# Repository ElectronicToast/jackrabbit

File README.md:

# jackrabbit

RP2040 16-channel 100 MHz logic analyzer

## Description
Jackrabbit is a RP2040-based 16-channel logic analyzer in a tiny 1.8" by 1.2" form factor. All digital inputs are buffered for compatibility with both 3V3 and 5V logic. Boot mode select and reset buttons are provided for convenience, and the ADC inputs and SWD pins are broken out. A USB-C connector is present for firmware updates and serial data.

## Documentation
- [Schematic](https://github.com/ElectronicToast/jackrabbit/blob/main/doc/jackrabbit.pdf)
- Fab print [front](https://github.com/ElectronicToast/jackrabbit/blob/main/doc/jackrabbit-f.pdf) and [back](https://github.com/ElectronicToast/jackrabbit/blob/main/doc/jackrabbit-b.pdf)
- [Interactive BOM](http://htmlpreview.github.io/?https://github.com/ElectronicToast/jackrabbit/blob/main/doc/ibom.html)

## Contributors
- Brian Cruz - BS EE, Caltech, 2023
- Brandon Gong - BS CECS, USC, 2024
- Ray Sun - BS EE, Caltech, 2020; PhD EE, USC, 2026

## Licensing
This project is released under the terms of the MIT License.

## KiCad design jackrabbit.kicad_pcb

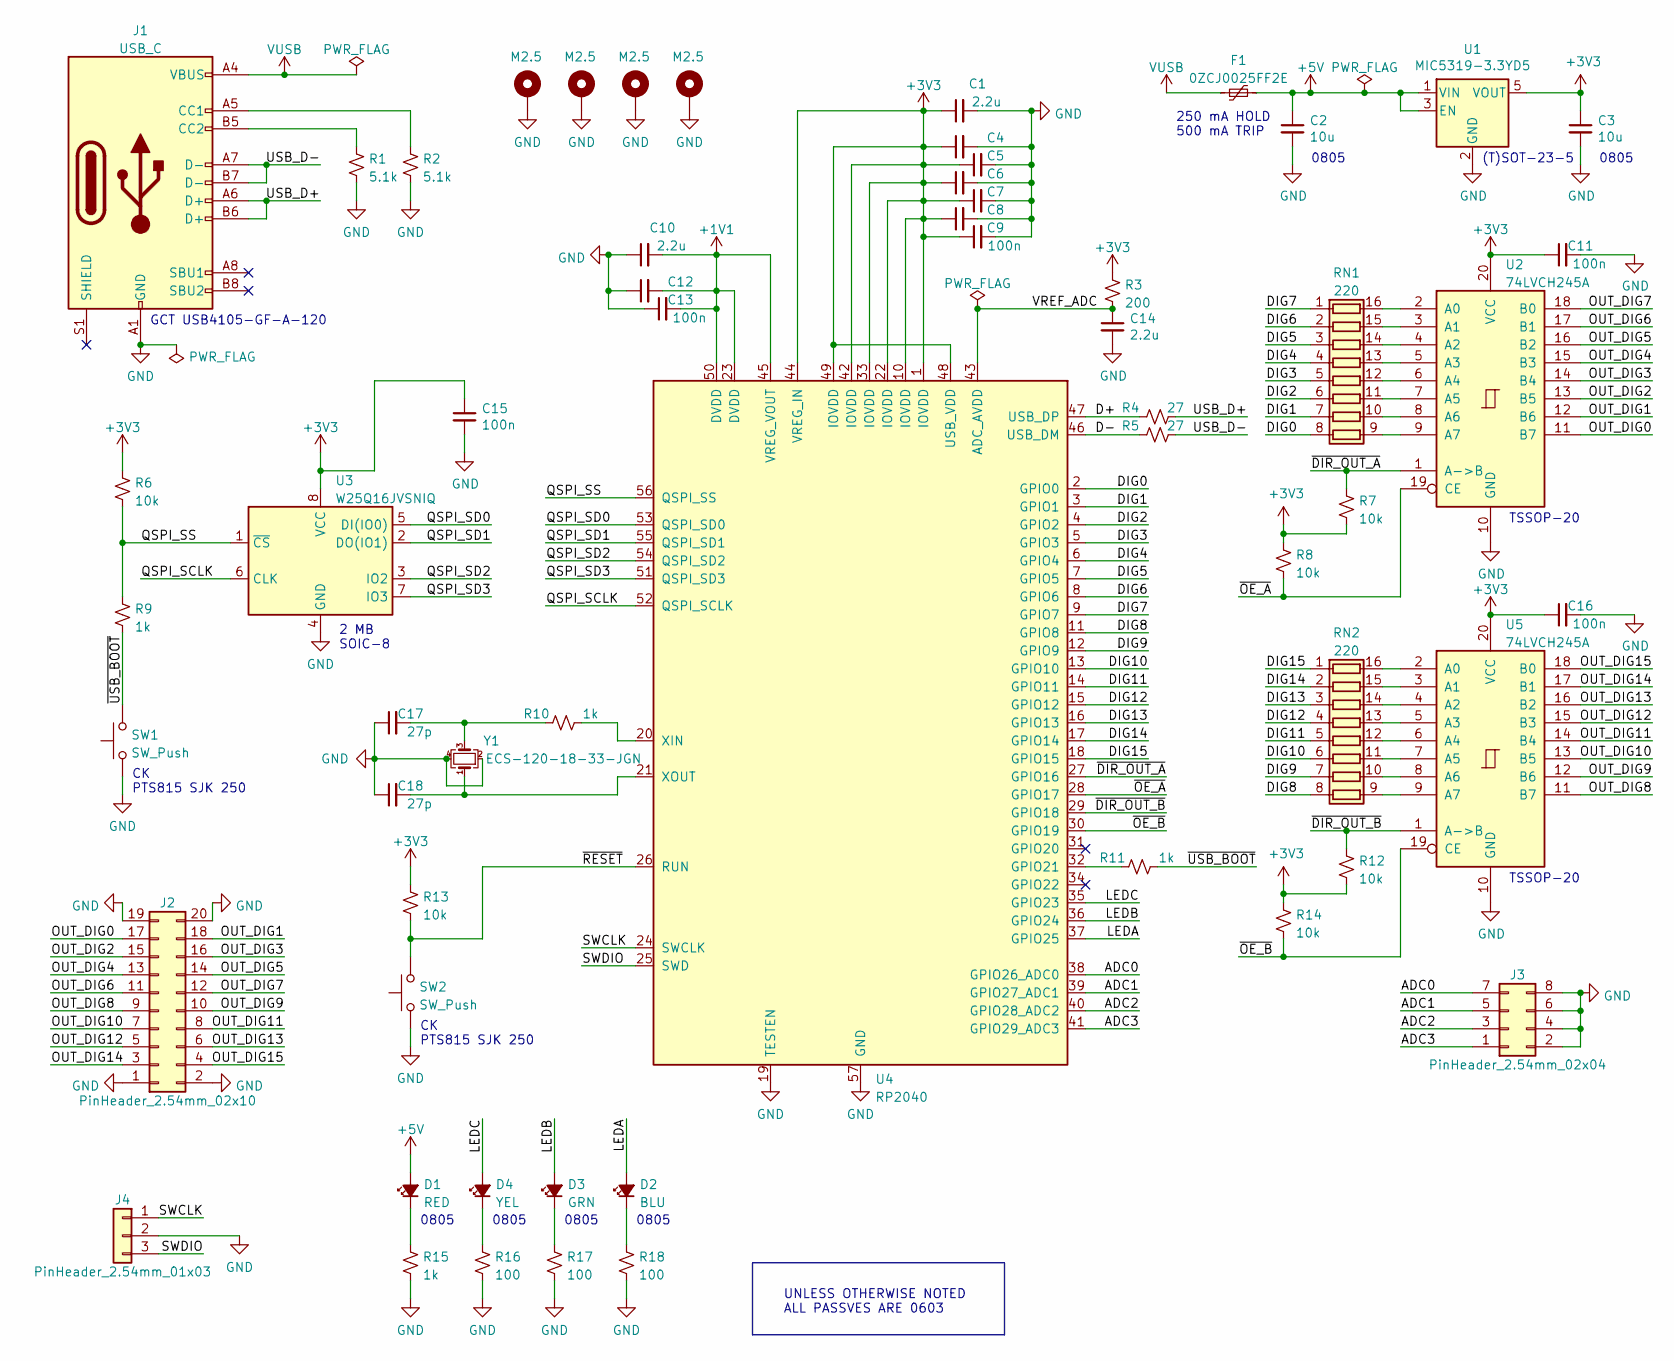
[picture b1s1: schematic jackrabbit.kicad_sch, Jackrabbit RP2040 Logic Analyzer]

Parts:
C1, C10, C14: 2.2u; C_0603_1608Metric_Pad1.08x0.95mm_HandSolder
C2, C3: 10u; C_0805_2012Metric_Pad1.18x1.45mm_HandSolder
C4, C5, C6, C7, C8, C9, C11, C12, C13, C15, C16: 100n; C_0603_1608Metric_Pad1.08x0.95mm_HandSolder
C17, C18: 27p; C_0603_1608Metric_Pad1.08x0.95mm_HandSolder
D1: RED; LED_0805_2012Metric_Pad1.15x1.40mm_HandSolder
D2: BLU; LED_0805_2012Metric_Pad1.15x1.40mm_HandSolder
D3: GRN; LED_0805_2012Metric_Pad1.15x1.40mm_HandSolder
D4: YEL; LED_0805_2012Metric_Pad1.15x1.40mm_HandSolder
F1: 0ZCJ0025FF2E; Fuse_1206_3216Metric_Pad1.42x1.75mm_HandSolder
H1, H2, H3, H4: M2.5; MountingHole_2.7mm_M2.5_Pad_Via
J1: USB_C; USB_C_Receptacle_GCT_USB4105-GF-A-120
J2: PinHeader_2.54mm_02x10; PinHeader_2x10_P2.54mm_Horizontal_NoSilk
J3: PinHeader_2.54mm_02x04; PinHeader_2x04_P2.54mm_NoSilk
J4: PinHeader_2.54mm_01x03; PinHeader_1x03_P2.54mm_NoSilk
R1, R2: 5.1k; R_0603_1608Metric_Pad0.98x0.95mm_HandSolder
R3: 200; R_0603_1608Metric_Pad0.98x0.95mm_HandSolder
R4, R5: 27; R_0603_1608Metric_Pad0.98x0.95mm_HandSolder
R6, R7, R8, R12, R13, R14: 10k; R_0603_1608Metric_Pad0.98x0.95mm_HandSolder
R9, R10, R11, R15: 1k; R_0603_1608Metric_Pad0.98x0.95mm_HandSolder
R16, R17, R18: 100; R_0603_1608Metric_Pad0.98x0.95mm_HandSolder
RN1, RN2: 220; R_Array_Convex_8x0602
SW1, SW2: SW_Push; SW_Push_CK_PTS815_HandSoldering
U1: MIC5319-3.3YD5; SOT-23-5
U2, U5: 74LVCH245A; TSSOP-20_4.4x5mm_P0.5mm
U3: W25Q16JVSNIQ; SOIC-8_3.9x4.9mm_P1.27mm
U4: RP2040; RP2040-QFN-56_HandSoldering
Y1: ECS-120-18-33-JGN; Crystal_SMD_ECS-4Pin_3.2x2.5mm

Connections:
+1V1: C10.2, C12.2, C13.2, U4.23 (DVDD), U4.45 (VREG_VOUT), U4.50 (DVDD)
+3V3: C1.1, C3.1, C4.1, C5.1, C6.1, C7.1, C8.1, C9.1, C11.1, C15.1, C16.1, R3.1, R6.1, R7.2, R8.1, R12.2, R13.1, R14.1, U1.5 (VOUT), U2.20 (VCC), U3.8 (VCC), U4.1 (IOVDD), U4.10 (IOVDD), U4.22 (IOVDD), U4.33 (IOVDD), U4.42 (IOVDD), U4.44 (VREG_IN), U4.48 (USB_VDD), U4.49 (IOVDD), U5.20 (VCC)
+5V: C2.1, D1.2 (A), F1.2, U1.1 (VIN), U1.3 (EN)
/ADC0: J3.7, U4.38 (GPIO26_ADC0)
/ADC1: J3.5, U4.39 (GPIO27_ADC1)
/ADC2: J3.3, U4.40 (GPIO28_ADC2)
/ADC3: J3.1, U4.41 (GPIO29_ADC3)
/D+: R4.1, U4.47 (USB_DP)
/D-: R5.1, U4.46 (USB_DM)
/DIG0: RN1.8 (R8.1), U4.2 (GPIO0)
/DIG1: RN1.7 (R7.1), U4.3 (GPIO1)
/DIG2: RN1.6 (R6.1), U4.4 (GPIO2)
/DIG3: RN1.5 (R5.1), U4.5 (GPIO3)
/DIG4: RN1.4 (R4.1), U4.6 (GPIO4)
/DIG5: RN1.3 (R3.1), U4.7 (GPIO5)
/DIG6: RN1.2 (R2.1), U4.8 (GPIO6)
/DIG7: RN1.1 (R1.1), U4.9 (GPIO7)
/DIG8: RN2.8 (R8.1), U4.11 (GPIO8)
/DIG9: RN2.7 (R7.1), U4.12 (GPIO9)
/DIG10: RN2.6 (R6.1), U4.13 (GPIO10)
/DIG11: RN2.5 (R5.1), U4.14 (GPIO11)
/DIG12: RN2.4 (R4.1), U4.15 (GPIO12)
/DIG13: RN2.3 (R3.1), U4.16 (GPIO13)
/DIG14: RN2.2 (R2.1), U4.17 (GPIO14)
/DIG15: RN2.1 (R1.1), U4.18 (GPIO15)
/LEDA: D2.2 (A), U4.37 (GPIO25)
/LEDB: D3.2 (A), U4.36 (GPIO24)
/LEDC: D4.2 (A), U4.35 (GPIO23)
/OUT_DIG0: J2.17, U2.11 (B7)
/OUT_DIG1: J2.18, U2.12 (B6)
/OUT_DIG2: J2.15, U2.13 (B5)
/OUT_DIG3: J2.16, U2.14 (B4)
/OUT_DIG4: J2.13, U2.15 (B3)
/OUT_DIG5: J2.14, U2.16 (B2)
/OUT_DIG6: J2.11, U2.17 (B1)
/OUT_DIG7: J2.12, U2.18 (B0)
/OUT_DIG8: J2.9, U5.11 (B7)
/OUT_DIG9: J2.10, U5.12 (B6)
/OUT_DIG10: J2.7, U5.13 (B5)
/OUT_DIG11: J2.8, U5.14 (B4)
/OUT_DIG12: J2.5, U5.15 (B3)
/OUT_DIG13: J2.6, U5.16 (B2)
/OUT_DIG14: J2.3, U5.17 (B1)
/OUT_DIG15: J2.4, U5.18 (B0)
/QSPI_SCLK: U3.6 (CLK), U4.52 (QSPI_SCLK)
/QSPI_SD0: U3.5 (DI(IO0)), U4.53 (QSPI_SD0)
/QSPI_SD1: U3.2 (DO(IO1)), U4.55 (QSPI_SD1)
/QSPI_SD2: U3.3 (IO2), U4.54 (QSPI_SD2)
/QSPI_SD3: U3.7 (IO3), U4.51 (QSPI_SD3)
/QSPI_SS: R6.2, R9.1, U3.1 (~CS), U4.56 (QSPI_SS)
/SWCLK: J4.1, U4.24 (SWCLK)
/SWDIO: J4.3, U4.25 (SWD)
/USB_D+: J1.A6 (D+), J1.B6 (D+), R4.2
/USB_D-: J1.A7 (D-), J1.B7 (D-), R5.2
/VREF_ADC: C14.1, R3.2, U4.43 (ADC_AVDD)
/~DIR_OUT_A: R7.1, U2.1 (A->B), U4.27 (GPIO16)
/~DIR_OUT_B: R12.1, U4.29 (GPIO18), U5.1 (A->B)
/~OE_A: R8.2, U2.19 (CE), U4.28 (GPIO17)
/~OE_B: R14.2, U4.30 (GPIO19), U5.19 (CE)
/~RESET: R13.2, SW2.2, U4.26 (RUN)
/~USB_BOOT: R9.2, R11.2, SW1.2
GND: C1.2, C2.2, C3.2, C4.2, C5.2, C6.2, C7.2, C8.2, C9.2, C10.1, C11.2, C12.1, C13.1, C14.2, C15.2, C16.2, C17.1, C18.1, H1.1, H2.1, H3.1, H4.1, J1.A1 (GND), J1.A12 (GND), J1.B1 (GND), J1.B12 (GND), J2.1, J2.2, J2.19, J2.20, J3.2, J3.4, J3.6, J3.8, J4.2, R1.2, R2.2, R15.2, R16.2, R17.2, R18.2, SW1.1, SW2.1, U1.2 (GND), U2.10 (GND), U3.4 (GND), U4.19 (TESTEN), U4.57 (GND), U5.10 (GND), Y1.2, Y1.4
unnamed: C17.2, R10.1, Y1.3
unnamed: C18.2, U4.21 (XOUT), Y1.1
unnamed: D1.1 (K), R15.1
unnamed: D2.1 (K), R18.1
unnamed: D3.1 (K), R17.1
unnamed: D4.1 (K), R16.1
unnamed: J1.A5 (CC1), R2.1
unnamed: J1.B5 (CC2), R1.1
unnamed: R10.2, U4.20 (XIN)
unnamed: R11.1, U4.32 (GPIO21)
unnamed: RN1.9 (R8.2), U2.9 (A7)
unnamed: RN1.10 (R7.2), U2.8 (A6)
unnamed: RN1.11 (R6.2), U2.7 (A5)
unnamed: RN1.12 (R5.2), U2.6 (A4)
unnamed: RN1.13 (R4.2), U2.5 (A3)
unnamed: RN1.14 (R3.2), U2.4 (A2)
unnamed: RN1.15 (R2.2), U2.3 (A1)
unnamed: RN1.16 (R1.2), U2.2 (A0)
unnamed: RN2.9 (R8.2), U5.9 (A7)
unnamed: RN2.10 (R7.2), U5.8 (A6)
unnamed: RN2.11 (R6.2), U5.7 (A5)
unnamed: RN2.12 (R5.2), U5.6 (A4)
unnamed: RN2.13 (R4.2), U5.5 (A3)
unnamed: RN2.14 (R3.2), U5.4 (A2)
unnamed: RN2.15 (R2.2), U5.3 (A1)
unnamed: RN2.16 (R1.2), U5.2 (A0)
VUSB: F1.1, J1.A4 (VBUS), J1.A9 (VBUS), J1.B4 (VBUS), J1.B9 (VBUS)

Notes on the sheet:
0805
CK PTS815 SJK 250
2 MB SOIC-8
UNLESS OTHERWISE NOTED ALL PASSVES ARE 0603
GCT USB4105-GF-A-120
250 mA HOLD 500 mA TRIP
TSSOP-20
(T)SOT-23-5

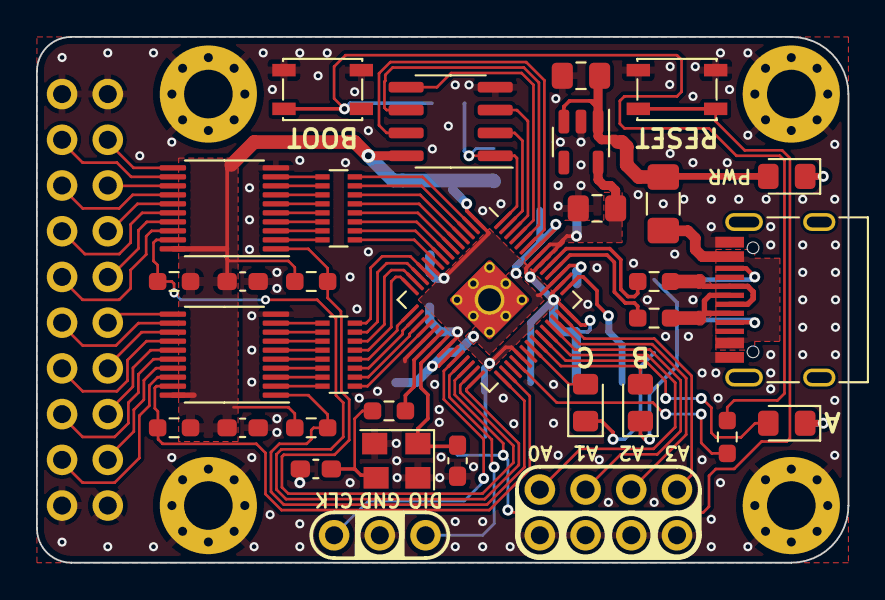
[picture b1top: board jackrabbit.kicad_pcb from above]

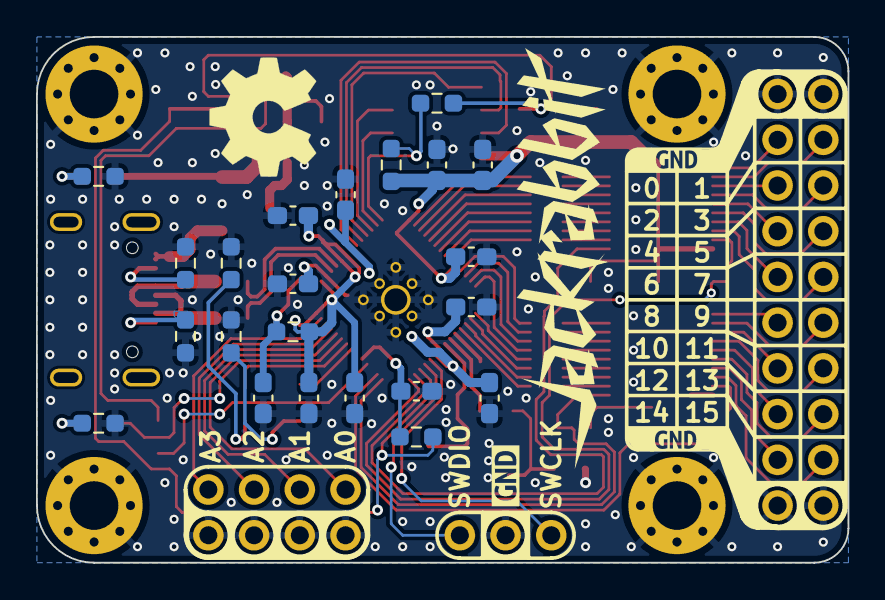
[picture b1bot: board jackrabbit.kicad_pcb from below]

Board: 2 copper layers, 45.1 x 29.2 mm, 63 parts (26 on the bottom side), 89 nets.

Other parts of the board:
kibuzzard-62E7A97F: G***; kibuzzard-62E7A97F
kibuzzard-62E7AE0F: G***; kibuzzard-62E7AE0F
kibuzzard-62E8C5F1, kibuzzard-62E8C5F1#2: G***; kibuzzard-62E8C5F1

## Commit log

2022-07-17 Add bus contention series protection resistors
2022-07-17 Start layout with passives on bottom
2022-07-17 Squeeze buffers together to lower board width
2022-07-22 Add pullups to disable buffers on power-on
2022-07-25 Redo placement to put USB and digital connector on long axis
2022-07-25 Change footprints to those of ordered parts
2022-07-26 Continue layout
2022-08-01 Continue layout; add labels for digital connector
2022-08-01 Add logos and connector labels
2022-08-01 Connect bootsel button to a GPIO; remove connectors for which we have no room
2022-08-02 Continue layout; prettify digital connector labels
2022-08-02 Flip LED labels to make 'A" the one by the USB connector
2022-08-11 Finish routing all traces
2022-08-12 Pass DRC
2022-09-13 Fix unconnected track end DRC warnings
2022-09-13 Replace 74LCX245 with 74LVCH245A for bus hold to prevent floating input
2022-09-13 Clean up board setup, increase thermal relief gap on THT pads
2022-09-15 Fix sheet and add OSHpark stackup info
2022-09-15 Fix pcb file for OSHpark
2022-09-15 Make crystal footprint; check footprints
2022-09-15 Generate documentation
2022-09-15 Generate ibon
2022-09-15 Make renders
